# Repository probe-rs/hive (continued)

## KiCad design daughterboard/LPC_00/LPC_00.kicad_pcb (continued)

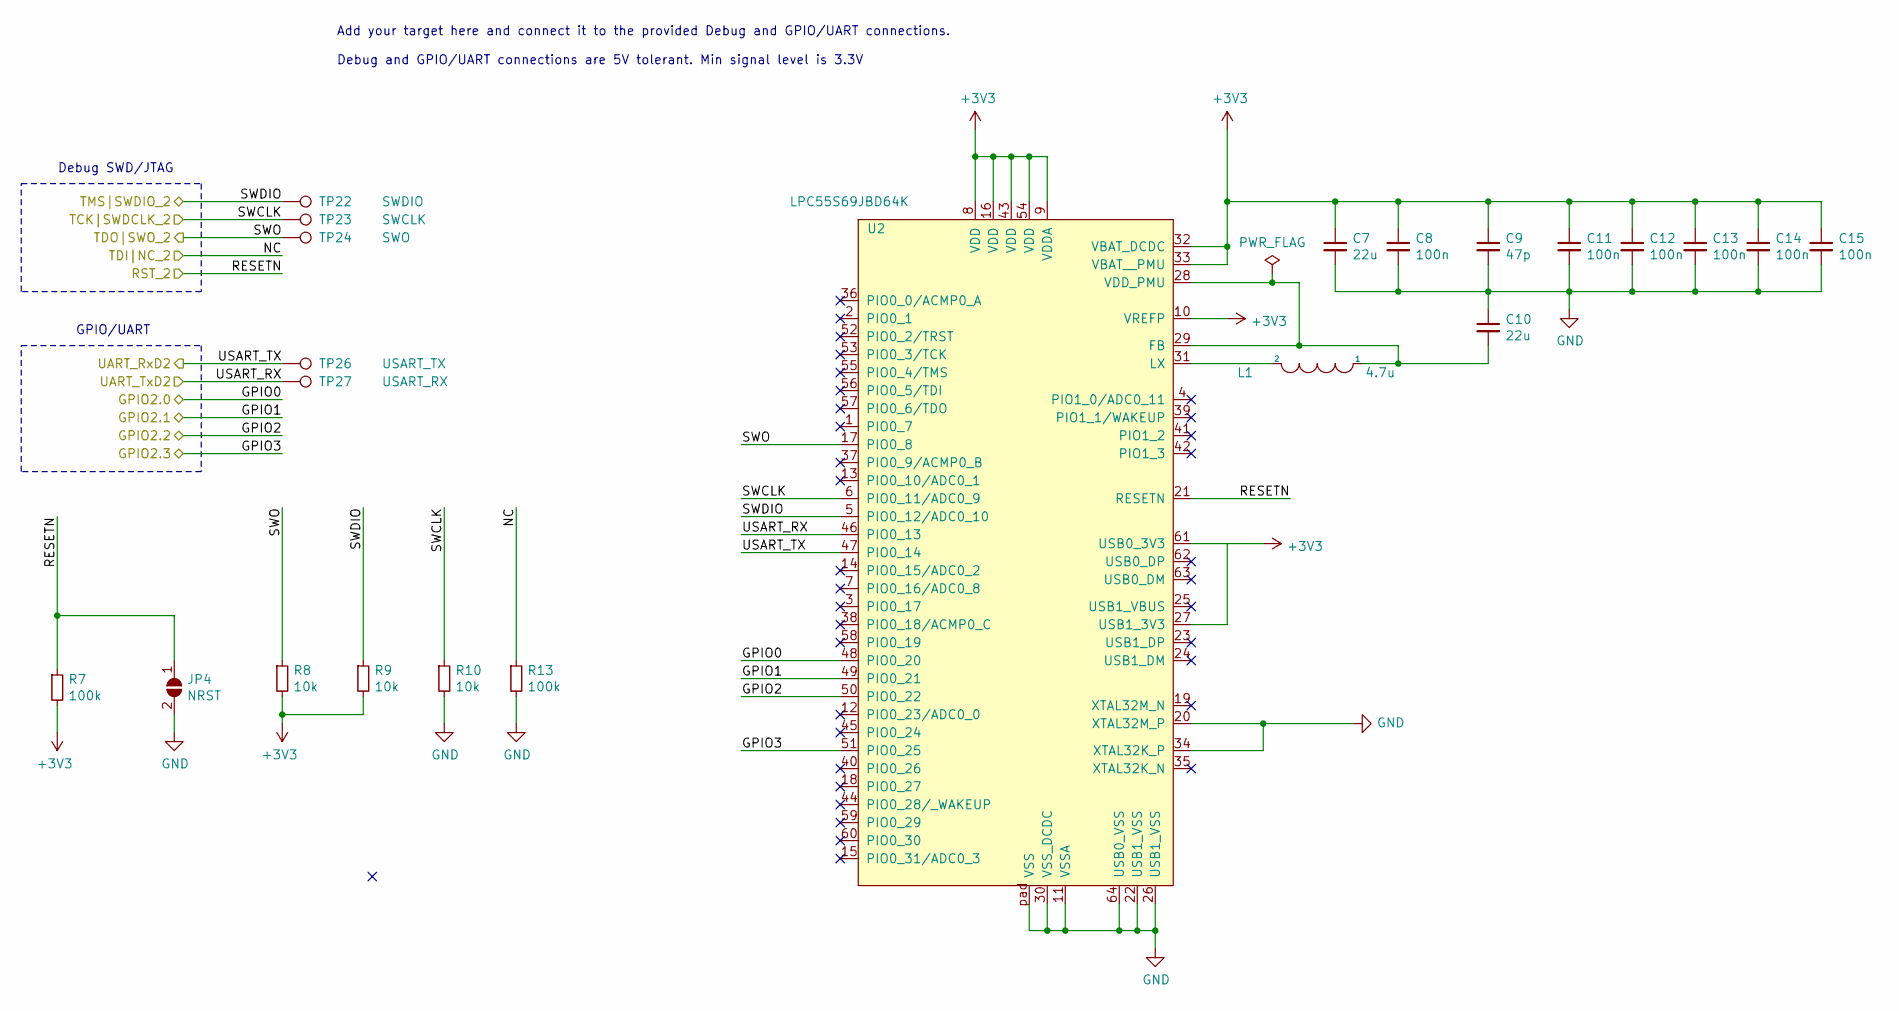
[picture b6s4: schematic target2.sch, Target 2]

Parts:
C7, C10: 22u; C_0603_1608Metric_Pad1.05x0.95mm_HandSolder
C8, C11, C12, C13, C14, C15: 100n; C_0603_1608Metric_Pad1.05x0.95mm_HandSolder
C9: 47p; C_0603_1608Metric_Pad1.05x0.95mm_HandSolder
JP4: NRST; SolderJumper-2_P1.3mm_Open_TrianglePad1.0x1.5mm
L1: 4.7u; TYA40204R7M-10
R7, R13: 100k; R_0603_1608Metric_Pad1.05x0.95mm_HandSolder
R8, R9, R10: 10k; R_0603_1608Metric_Pad1.05x0.95mm_HandSolder
TP22: SWDIO; TestPoint_Pad_1.0x1.0mm
TP23: SWCLK; TestPoint_Pad_1.0x1.0mm
TP24: SWO; TestPoint_Pad_1.0x1.0mm
TP26: USART_TX; TestPoint_Pad_1.0x1.0mm
TP27: USART_RX; TestPoint_Pad_1.0x1.0mm
U2: LPC55S69JBD64K

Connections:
+3V3: C7.1, C8.1, C9.1, C11.1, C12.1, C13.1, C14.1, C15.1, R7.2, R8.2, R9.2, U2.8 (VDD), U2.9 (VDDA), U2.10 (VREFP), U2.16 (VDD), U2.27 (USB1_3V3), U2.32 (VBAT_DCDC), U2.33 (VBAT__PMU), U2.43 (VDD), U2.54 (VDD), U2.61 (USB0_3V3); also elsewhere on the board
/Target 2/GPIO2.0: U2.48 (PIO0_20); also elsewhere on the board
/Target 2/GPIO2.1: U2.49 (PIO0_21); also elsewhere on the board
/Target 2/GPIO2.2: U2.50 (PIO0_22); also elsewhere on the board
/Target 2/GPIO2.3: U2.51 (PIO0_25); also elsewhere on the board
/Target 2/RST_2: JP4.1 (A), R7.1, U2.21 (RESETN); also elsewhere on the board
/Target 2/TCK|SWDCLK_2: R10.1, TP23.1, U2.6 (PIO0_11/ADC0_9); also elsewhere on the board
/Target 2/TDI|NC_2: R13.1; also elsewhere on the board
/Target 2/TDO|SWO_2: R8.1, TP24.1, U2.17 (PIO0_8); also elsewhere on the board
/Target 2/TMS|SWDIO_2: R9.1, TP22.1, U2.5 (PIO0_12/ADC0_10); also elsewhere on the board
/Target 2/UART_RxD2: TP26.1, U2.47 (PIO0_14); also elsewhere on the board
/Target 2/UART_TxD2: TP27.1, U2.46 (PIO0_13); also elsewhere on the board
GND: C7.2, C8.2, C9.2, C10.1, C11.2, C12.2, C13.2, C14.2, C15.2, JP4.2 (B), R10.2, R13.2, U2.11 (VSSA), U2.20 (XTAL32M_P), U2.22 (USB1_VSS), U2.26 (USB1_VSS), U2.30 (VSS_DCDC), U2.34 (XTAL32K_P), U2.64 (USB0_VSS), U2.pad (VSS); also elsewhere on the board
unnamed: C10.2, L1.1, U2.28 (VDD_PMU), U2.29 (FB)
unnamed: L1.2, U2.31 (LX)

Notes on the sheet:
Debug SWD/JTAG
GPIO/UART
Add your target here and connect it to the provided Debug and GPIO/UART connections. Debug and GPIO/UART connections are 5V tolerant. Min signal level is 3.3V

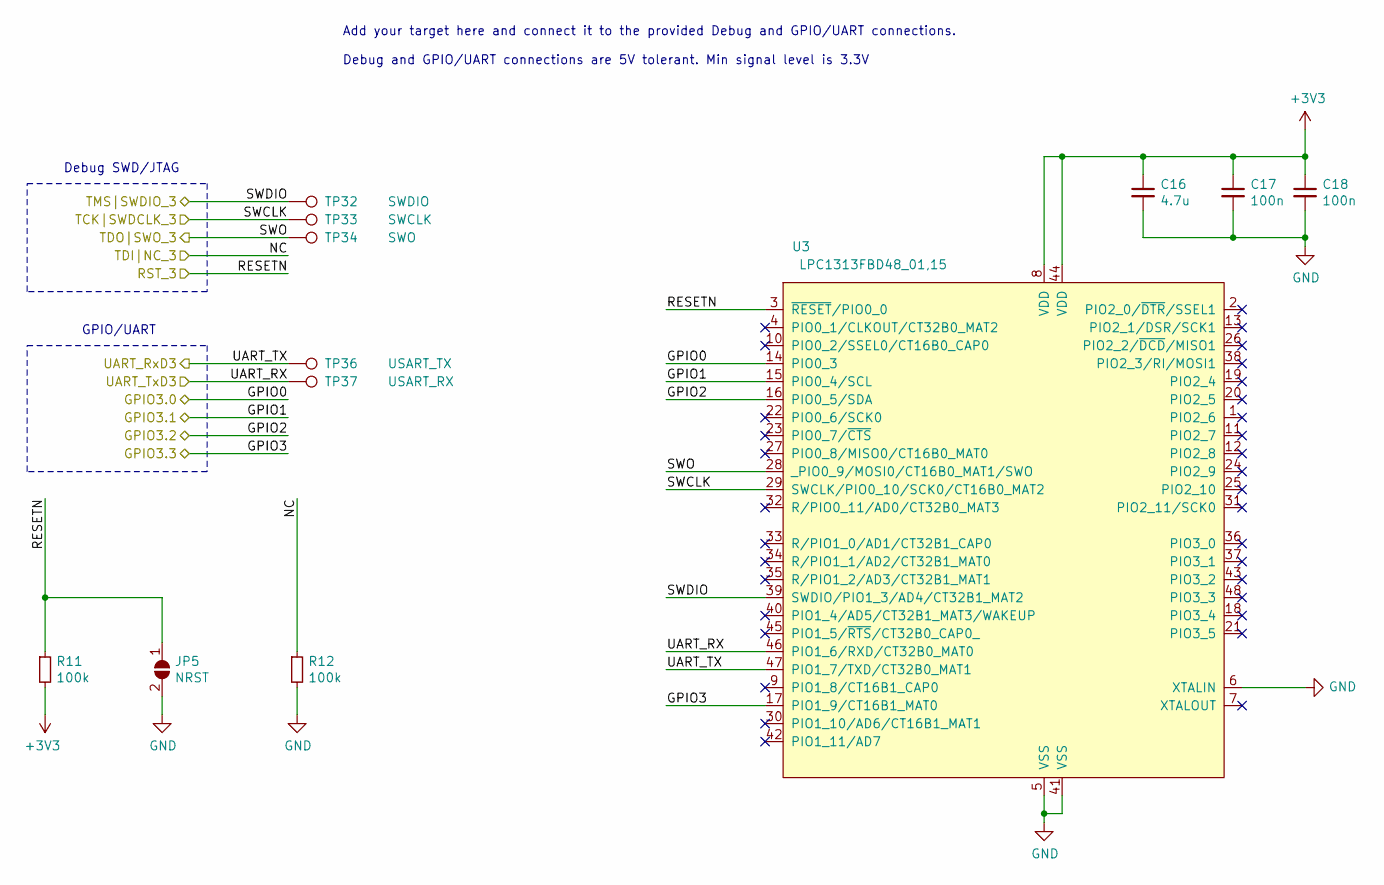
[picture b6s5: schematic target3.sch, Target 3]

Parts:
C16: 4.7u; C_0603_1608Metric_Pad1.05x0.95mm_HandSolder
C17, C18: 100n; C_0603_1608Metric_Pad1.05x0.95mm_HandSolder
JP5: NRST; SolderJumper-2_P1.3mm_Open_TrianglePad1.0x1.5mm
R11, R12: 100k; R_0603_1608Metric_Pad1.05x0.95mm_HandSolder
TP32: SWDIO; TestPoint_Pad_1.0x1.0mm
TP33: SWCLK; TestPoint_Pad_1.0x1.0mm
TP34: SWO; TestPoint_Pad_1.0x1.0mm
TP36: USART_TX; TestPoint_Pad_1.0x1.0mm
TP37: USART_RX; TestPoint_Pad_1.0x1.0mm
U3: LPC1313FBD48_01,15; LPC1313FBD48_0115

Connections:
+3V3: C16.1, C17.1, C18.1, R11.2, U3.8 (VDD), U3.44 (VDD); also elsewhere on the board
/Target 3/GPIO3.0: U3.14 (PIO0_3); also elsewhere on the board
/Target 3/GPIO3.1: U3.15 (PIO0_4/SCL); also elsewhere on the board
/Target 3/GPIO3.2: U3.16 (PIO0_5/SDA); also elsewhere on the board
/Target 3/GPIO3.3: U3.17 (PIO1_9/CT16B1_MAT0); also elsewhere on the board
/Target 3/RST_3: JP5.1 (A), R11.1, U3.3 (~RESET~/PIO0_0); also elsewhere on the board
/Target 3/TCK|SWDCLK_3: TP33.1, U3.29 (SWCLK/PIO0_10/SCK0/CT16B0_MAT2); also elsewhere on the board
/Target 3/TDI|NC_3: R12.1; also elsewhere on the board
/Target 3/TDO|SWO_3: TP34.1, U3.28 (_PIO0_9/MOSI0/CT16B0_MAT1/SWO); also elsewhere on the board
/Target 3/TMS|SWDIO_3: TP32.1, U3.39 (SWDIO/PIO1_3/AD4/CT32B1_MAT2); also elsewhere on the board
/Target 3/UART_RxD3: TP36.1, U3.47 (PIO1_7/TXD/CT32B0_MAT1); also elsewhere on the board
/Target 3/UART_TxD3: TP37.1, U3.46 (PIO1_6/RXD/CT32B0_MAT0); also elsewhere on the board
GND: C16.2, C17.2, C18.2, JP5.2 (B), R12.2, U3.5 (VSS), U3.6 (XTALIN), U3.41 (VSS); also elsewhere on the board

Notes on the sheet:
Debug SWD/JTAG
GPIO/UART
Add your target here and connect it to the provided Debug and GPIO/UART connections. Debug and GPIO/UART connections are 5V tolerant. Min signal level is 3.3V

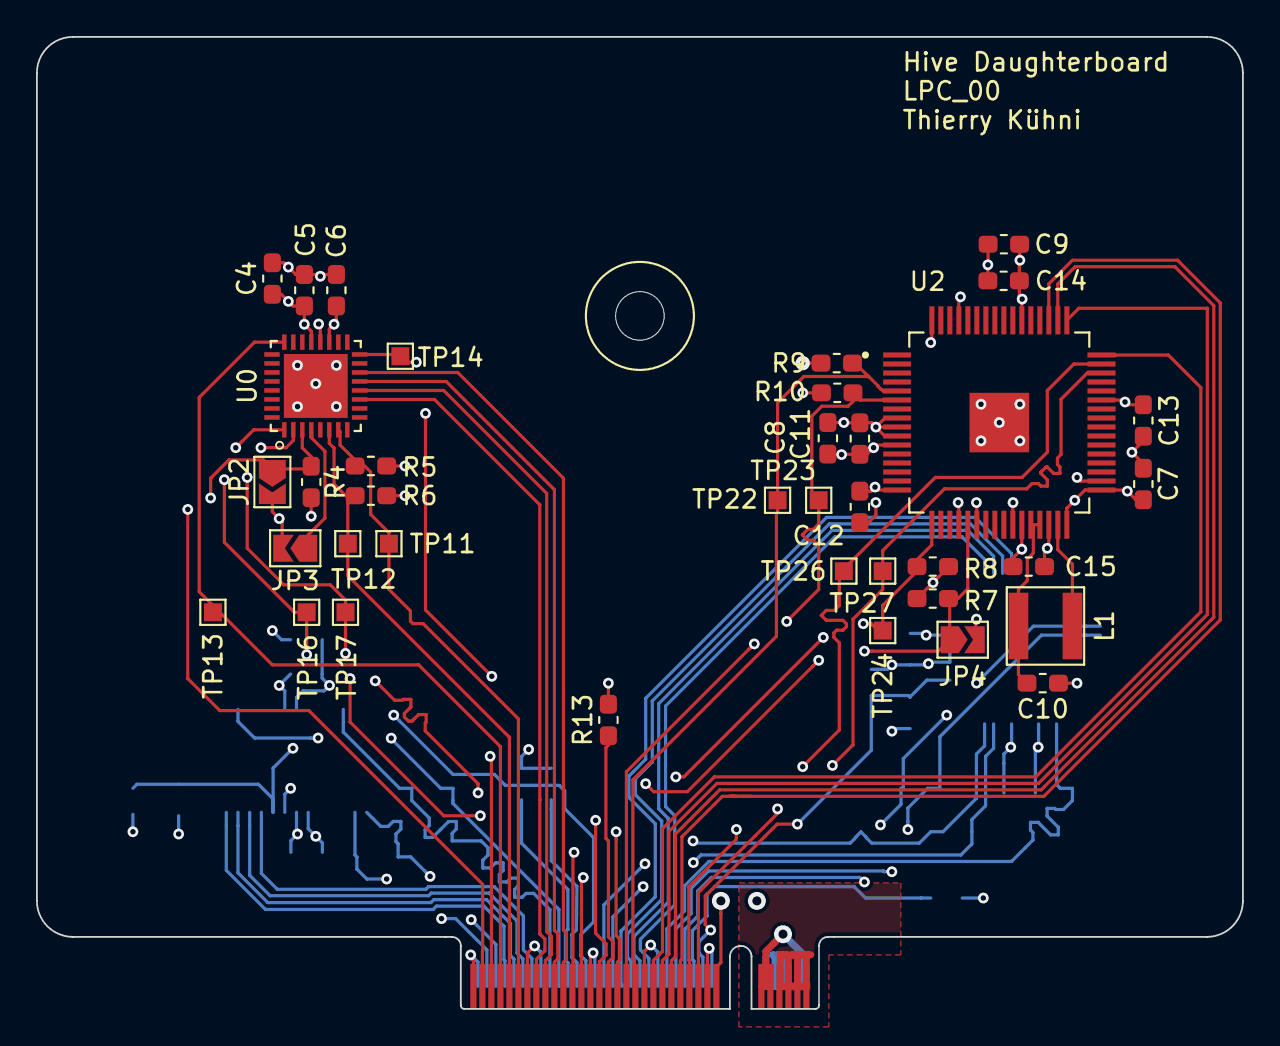
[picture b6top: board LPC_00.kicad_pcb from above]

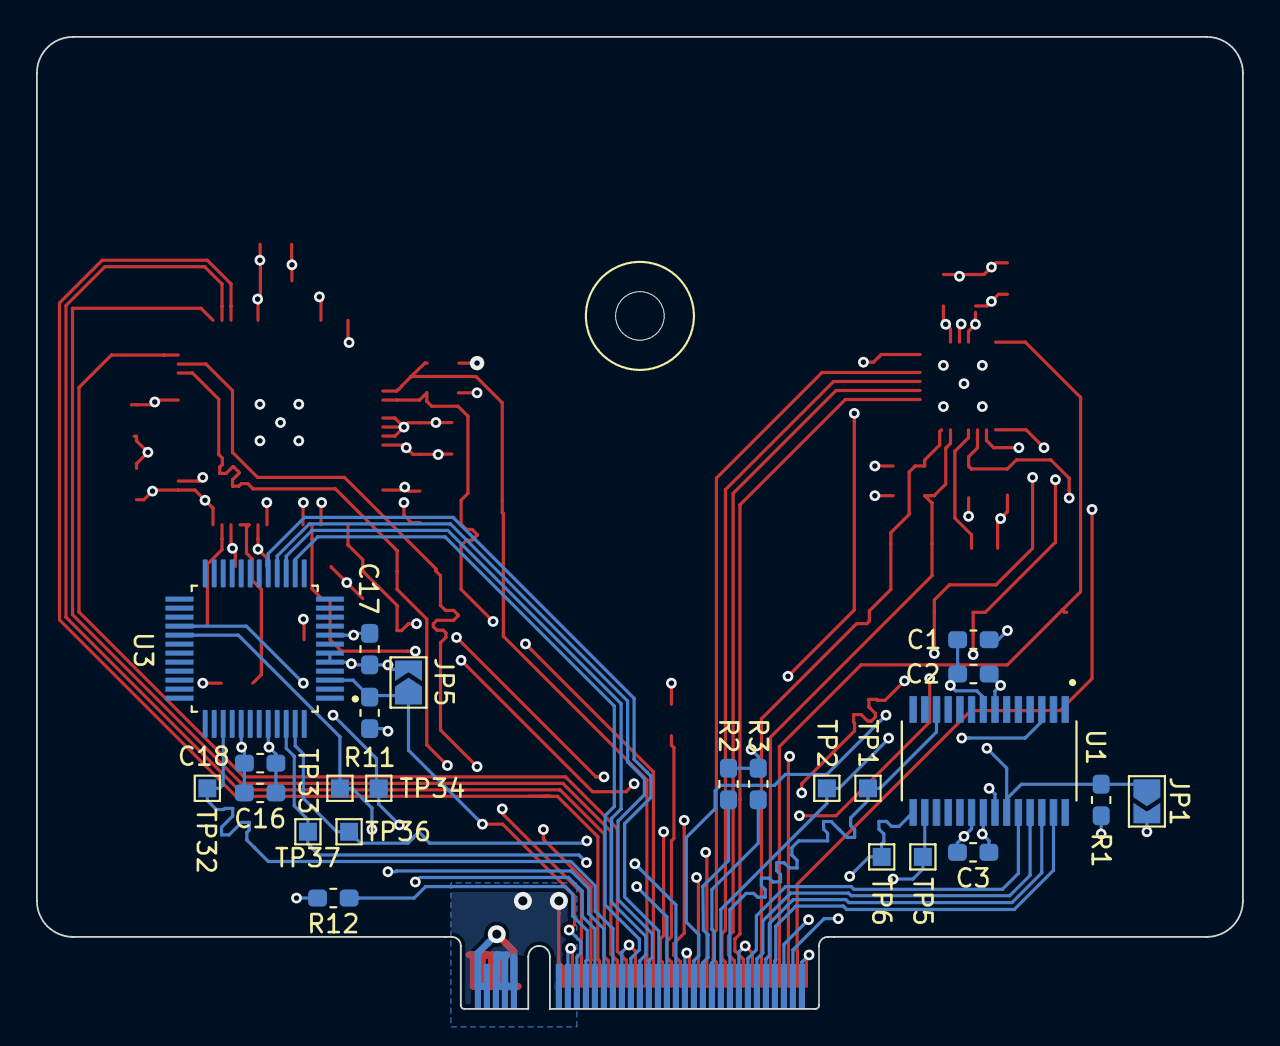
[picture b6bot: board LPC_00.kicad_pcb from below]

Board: 4 copper layers, 67.0 x 54.0 mm, 63 parts (24 on the bottom side), 50 nets.

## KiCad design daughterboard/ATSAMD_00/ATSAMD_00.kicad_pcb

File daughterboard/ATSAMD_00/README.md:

## ATSAMD_00
A daughterboard which contains a selection of ATSAMD MCUs.

### Targets
The following targets are implemented on this Daughterboard:
| Designation | MCU |
| --- | --- |
| target0 | ATSAMD10C13A-SSUT |
| target1 | ATSAMD09D14A-MUT |
| target2 | ATSAMD51J18A-AU |
| target3 | ATSAMD21E16L-AFT |

### Partlist
The partlist for this Daughterboard is available [here](https://octopart.com/bom-tool/9WbPLhTP).

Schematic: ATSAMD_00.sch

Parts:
H1: MountingHoleDaughterboard; MountingHole_2.7mm_M2.5
J1: m2_keyA_67pin_daughterboard; m2_keyB

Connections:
+3V3: J1.6 (+3V3), J1.8 (+3V3), J1.10 (+3V3), J1.20 (+3V3), J1.21 (BOARD_DETECT); also elsewhere on the board
+5V: J1.1 (+5V), J1.3 (+5V), J1.5 (+5V), J1.7 (+5V)
/Target 0/GPIO0.0: J1.61 (TGT_GPIO0.0); also elsewhere on the board
/Target 0/GPIO0.1: J1.59 (TGT_GPIO0.1); also elsewhere on the board
/Target 0/GPIO0.2: J1.57 (TGT_GPIO0.2); also elsewhere on the board
/Target 0/GPIO0.3: J1.55 (TGT_GPIO0.3); also elsewhere on the board
/Target 0/RST_0: J1.73 (TGT_RST_0); also elsewhere on the board
/Target 0/TCK|SWDCLK_0: J1.67 (TGT_TCK|SWDCLK_0); also elsewhere on the board
/Target 0/TDI|NC_0: J1.71 (TGT_TDI|NC_0); also elsewhere on the board
/Target 0/TDO|SWO_0: J1.69 (TGT_TDO|SWO_0); also elsewhere on the board
/Target 0/TMS|SWDIO_0: J1.65 (TGT_TMS|SWDIO_0); also elsewhere on the board
/Target 0/UART_RxD0: J1.51 (TGT_UART_RxD0); also elsewhere on the board
/Target 0/UART_TxD0: J1.53 (TGT_UART_TxD0); also elsewhere on the board
/Target 1/GPIO1.0: J1.62 (TGT_GPIO1.0); also elsewhere on the board
/Target 1/GPIO1.1: J1.64 (TGT_GPIO1.1); also elsewhere on the board
/Target 1/GPIO1.2: J1.66 (TGT_GPIO1.2); also elsewhere on the board
/Target 1/GPIO1.3: J1.68 (TGT_GPIO1.3); also elsewhere on the board
/Target 1/RST_1: J1.50 (TGT_RST_1); also elsewhere on the board
/Target 1/TCK|SWDCLK_1: J1.56 (TGT_TCK|SWDCLK_1); also elsewhere on the board
/Target 1/TDI|NC_1: J1.52 (TGT_TDI|NC_1); also elsewhere on the board
/Target 1/TDO|SWO_1: J1.54 (TGT_TDO|SWO_1); also elsewhere on the board
/Target 1/TMS|SWDIO_1: J1.58 (TGT_TMS|SWDIO_1); also elsewhere on the board
/Target 1/UART_RxD1: J1.72 (TGT_UART_RxD1); also elsewhere on the board
/Target 1/UART_TxD1: J1.70 (TGT_UART_TxD1); also elsewhere on the board
/Target 2/GPIO2.0: J1.35 (TGT_GPIO2.0); also elsewhere on the board
/Target 2/GPIO2.1: J1.33 (TGT_GPIO2.1); also elsewhere on the board
/Target 2/GPIO2.2: J1.31 (TGT_GPIO2.2); also elsewhere on the board
/Target 2/GPIO2.3: J1.29 (TGT_GPIO2.3); also elsewhere on the board
/Target 2/RST_2: J1.47 (TGT_RST_2); also elsewhere on the board
/Target 2/TCK|SWDCLK_2: J1.41 (TGT_TCK|SWDCLK_2); also elsewhere on the board
/Target 2/TDI|NC_2: J1.45 (TGT_TDI|NC_2); also elsewhere on the board
/Target 2/TDO|SWO_2: J1.43 (TGT_TDO|SWO_2); also elsewhere on the board
/Target 2/TMS|SWDIO_2: J1.39 (TGT_TMS|SWDIO_2); also elsewhere on the board
/Target 2/UART_RxD2: J1.25 (TGT_UART_RxD2); also elsewhere on the board
/Target 2/UART_TxD2: J1.27 (TGT_UART_TxD2); also elsewhere on the board
/Target 3/GPIO3.0: J1.36 (TGT_GPIO3.0); also elsewhere on the board
/Target 3/GPIO3.1: J1.38 (TGT_GPIO3.1); also elsewhere on the board
/Target 3/GPIO3.2: J1.40 (TGT_GPIO3.2); also elsewhere on the board
/Target 3/GPIO3.3: J1.42 (TGT_GPIO3.3); also elsewhere on the board
/Target 3/RST_3: J1.24 (TGT_RST_3); also elsewhere on the board
/Target 3/TCK|SWDCLK_3: J1.30 (TGT_TCK|SWDCLK_3); also elsewhere on the board
/Target 3/TDI|NC_3: J1.26 (TGT_TDI|NC_3); also elsewhere on the board
/Target 3/TDO|SWO_3: J1.28 (TGT_TDO|SWO_3); also elsewhere on the board
/Target 3/TMS|SWDIO_3: J1.32 (TGT_TMS|SWDIO_3); also elsewhere on the board
/Target 3/UART_RxD3: J1.46 (TGT_UART_RxD3); also elsewhere on the board
/Target 3/UART_TxD3: J1.44 (TGT_UART_TxD3); also elsewhere on the board
GND: J1.2 (GND), J1.4 (GND), J1.9 (GND), J1.11 (GND), J1.22 (GND), J1.23 (GND), J1.34 (GND), J1.37 (GND), J1.48 (GND), J1.49 (GND), J1.60 (GND), J1.63 (GND), J1.74 (GND), J1.75 (GND); also elsewhere on the board

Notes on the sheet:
You can implement 4 targets per daugtherboard. Please use the corresponding hierarchical schematics for that.

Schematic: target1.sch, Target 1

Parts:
C1, C3: 100n; C_0603_1608Metric_Pad1.05x0.95mm_HandSolder
C2: 4.7u; C_0603_1608Metric_Pad1.05x0.95mm_HandSolder
JP1: NRST; SolderJumper-2_P1.3mm_Open_TrianglePad1.0x1.5mm
R1: 10k; R_0603_1608Metric_Pad1.05x0.95mm_HandSolder
R2: 330; R_0603_1608Metric_Pad1.05x0.95mm_HandSolder
R3: 1k; R_0603_1608Metric_Pad1.05x0.95mm_HandSolder
R4, R5: 100k; R_0603_1608Metric_Pad1.05x0.95mm_HandSolder
TP1: SWDIO; TestPoint_Pad_1.0x1.0mm
TP2: SWCLK; TestPoint_Pad_1.0x1.0mm
TP5: USART_TX; TestPoint_Pad_1.0x1.0mm
TP6: USART_RX; TestPoint_Pad_1.0x1.0mm
U1: ATSAMD09D14A-M; QFN-24-1EP_4x4mm_P0.5mm_EP2.6x2.6mm

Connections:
+3V3: C2.1, C3.1, R1.2, R3.2, U1.24 (VDD); also elsewhere on the board
/Target 1/GPIO1.0: U1.9 (PA10); also elsewhere on the board
/Target 1/GPIO1.1: U1.10 (PA11); also elsewhere on the board
/Target 1/GPIO1.2: U1.11 (PA14); also elsewhere on the board
/Target 1/GPIO1.3: U1.12 (PA15); also elsewhere on the board
/Target 1/RST_1: C1.1, R1.1, R2.2, U1.18 (PA28/~RST); also elsewhere on the board
/Target 1/TCK|SWDCLK_1: R3.1, TP2.1, U1.19 (PA30/SWCLK); also elsewhere on the board
/Target 1/TDI|NC_1: R4.1; also elsewhere on the board
/Target 1/TDO|SWO_1: R5.1; also elsewhere on the board
/Target 1/TMS|SWDIO_1: TP1.1, U1.20 (PA31/SWDIO); also elsewhere on the board
/Target 1/UART_RxD1: TP5.1, U1.3 (PA04); also elsewhere on the board
/Target 1/UART_TxD1: TP6.1, U1.5 (PA06); also elsewhere on the board
GND: C1.2, C2.2, C3.2, JP1.1 (A), R4.2, R5.2, U1.23 (GND); also elsewhere on the board
unnamed: JP1.2 (B), R2.1

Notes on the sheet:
Debug SWD/JTAG
GPIO/UART
Add your target here and connect it to the provided Debug and GPIO/UART connections. Debug and GPIO/UART connections are 5V tolerant. Min signal level is 3.3V

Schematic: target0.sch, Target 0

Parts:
C4, C6: 100n; C_0603_1608Metric_Pad1.05x0.95mm_HandSolder
C5: 4.7u; C_0603_1608Metric_Pad1.05x0.95mm_HandSolder
JP2: NRST; SolderJumper-2_P1.3mm_Open_TrianglePad1.0x1.5mm
R6: 10k; R_0603_1608Metric_Pad1.05x0.95mm_HandSolder
R7: 330; R_0603_1608Metric_Pad1.05x0.95mm_HandSolder
R8: 1k; R_0603_1608Metric_Pad1.05x0.95mm_HandSolder
R9, R10: 100k; R_0603_1608Metric_Pad1.05x0.95mm_HandSolder
TP11: SWDIO; TestPoint_Pad_1.0x1.0mm
TP12: SWCLK; TestPoint_Pad_1.0x1.0mm
TP15: USART_TX; TestPoint_Pad_1.0x1.0mm
TP16: USART_RX; TestPoint_Pad_1.0x1.0mm
U0: ATSAMD10C13A-SS; SOIC-14_3.9x8.7mm_P1.27mm

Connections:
+3V3: C5.1, C6.1, R6.2, R8.2, U0.12 (VDD); also elsewhere on the board
/Target 0/GPIO0.0: U0.9 (PA24); also elsewhere on the board
/Target 0/GPIO0.1: U0.10 (PA25); also elsewhere on the board
/Target 0/GPIO0.2: U0.13 (PA02); also elsewhere on the board
/Target 0/GPIO0.3: U0.14 (PA04); also elsewhere on the board
/Target 0/RST_0: C4.1, R6.1, R7.2, U0.6 (PA28/~RST); also elsewhere on the board
/Target 0/TCK|SWDCLK_0: R8.1, TP12.1, U0.7 (PA30/SWCLK); also elsewhere on the board
/Target 0/TDI|NC_0: R9.1; also elsewhere on the board
/Target 0/TDO|SWO_0: R10.1; also elsewhere on the board
/Target 0/TMS|SWDIO_0: TP11.1, U0.8 (PA31/SWDIO); also elsewhere on the board
/Target 0/UART_RxD0: TP15.1, U0.4 (PA14); also elsewhere on the board
/Target 0/UART_TxD0: TP16.1, U0.1 (PA05); also elsewhere on the board
GND: C4.2, C5.2, C6.2, JP2.1 (A), R9.2, R10.2, U0.11 (GND); also elsewhere on the board
unnamed: JP2.2 (B), R7.1

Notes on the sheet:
Debug SWD/JTAG
GPIO/UART
Add your target here and connect it to the provided Debug and GPIO/UART connections. Debug and GPIO/UART connections are 5V tolerant. Min signal level is 3.3V

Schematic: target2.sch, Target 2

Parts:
C7, C8, C12, C13, C14, C20: 100n; C_0603_1608Metric_Pad1.05x0.95mm_HandSolder
C9: 4.7u; C_0603_1608Metric_Pad1.05x0.95mm_HandSolder
C10: 10u; C_0603_1608Metric_Pad1.05x0.95mm_HandSolder
C11: 1u; C_0603_1608Metric_Pad1.05x0.95mm_HandSolder
JP3: NRST; SolderJumper-2_P1.3mm_Open_TrianglePad1.0x1.5mm
R11: 10k; R_0603_1608Metric_Pad1.05x0.95mm_HandSolder
R12: 330; R_0603_1608Metric_Pad1.05x0.95mm_HandSolder
R13: 1k; R_0603_1608Metric_Pad1.05x0.95mm_HandSolder
R14: 100k; R_0603_1608Metric_Pad1.05x0.95mm_HandSolder
TP21: SWDIO; TestPoint_Pad_1.0x1.0mm
TP22: SWCLK; TestPoint_Pad_1.0x1.0mm
TP23: SWO; TestPoint_Pad_1.0x1.0mm
TP25: USART_TX; TestPoint_Pad_1.0x1.0mm
TP26: USART_RX; TestPoint_Pad_1.0x1.0mm
U2: ATSAMD51J18A-A; TQFP-64_10x10mm_P0.5mm

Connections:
+3V3: C10.1, C11.1, C12.1, C13.1, C14.1, C20.1, R11.2, R13.2, U2.8 (VDDANA), U2.21 (VDDIOB), U2.34 (VDDIO), U2.48 (VDDIO), U2.56 (VDDIO); also elsewhere on the board
/Target 2/GPIO2.0: U2.1 (PA00); also elsewhere on the board
/Target 2/GPIO2.1: U2.2 (PA01); also elsewhere on the board
/Target 2/GPIO2.2: U2.3 (PA02); also elsewhere on the board
/Target 2/GPIO2.3: U2.4 (PA03); also elsewhere on the board
/Target 2/RST_2: C7.1, R11.1, R12.2, U2.52 (~RESET); also elsewhere on the board
/Target 2/TCK|SWDCLK_2: R13.1, TP22.1, U2.57 (PA30); also elsewhere on the board
/Target 2/TDI|NC_2: R14.1; also elsewhere on the board
/Target 2/TDO|SWO_2: TP23.1, U2.59 (PB30); also elsewhere on the board
/Target 2/TMS|SWDIO_2: TP21.1, U2.58 (PA31); also elsewhere on the board
/Target 2/UART_RxD2: TP25.1, U2.35 (PA16); also elsewhere on the board
/Target 2/UART_TxD2: TP26.1, U2.37 (PA18); also elsewhere on the board
GND: C7.2, C8.2, C9.2, C10.2, C11.2, C12.2, C13.2, C14.2, C20.2, JP3.1 (A), R14.2, U2.7 (GNDANA), U2.22 (GND), U2.33 (GND), U2.47 (GND), U2.54 (GND); also elsewhere on the board
unnamed: C8.1, C9.1, U2.53 (VDDCORE)
unnamed: JP3.2 (B), R12.1

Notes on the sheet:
Debug SWD/JTAG
GPIO/UART
Add your target here and connect it to the provided Debug and GPIO/UART connections. Debug and GPIO/UART connections are 5V tolerant. Min signal level is 3.3V

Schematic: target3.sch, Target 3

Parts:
C15, C18, C19: 100n; C_0603_1608Metric_Pad1.05x0.95mm_HandSolder
C16: 1u; C_0603_1608Metric_Pad1.05x0.95mm_HandSolder
C17: 10u; C_0603_1608Metric_Pad1.05x0.95mm_HandSolder
JP4: NRST; SolderJumper-2_P1.3mm_Open_TrianglePad1.0x1.5mm
R15: 10k; R_0603_1608Metric_Pad1.05x0.95mm_HandSolder
R16: 330; R_0603_1608Metric_Pad1.05x0.95mm_HandSolder
R17: 1k; R_0603_1608Metric_Pad1.05x0.95mm_HandSolder
R18, R19: 100k; R_0603_1608Metric_Pad1.05x0.95mm_HandSolder
TP31: SWDIO; TestPoint_Pad_1.0x1.0mm
TP32: SWCLK; TestPoint_Pad_1.0x1.0mm
TP35: USART_TX; TestPoint_Pad_1.0x1.0mm
TP36: USART_RX; TestPoint_Pad_1.0x1.0mm
U3: ATSAMD21E16L-AFT

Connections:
+3V3: C17.1, C18.1, C19.1, R15.2, R17.2, U3.9 (VDDIO/ANA), U3.28 (VDDIO); also elsewhere on the board
/Target 3/GPIO3.0: U3.17 (PA16); also elsewhere on the board
/Target 3/GPIO3.1: U3.18 (PA17); also elsewhere on the board
/Target 3/GPIO3.2: U3.19 (PA18); also elsewhere on the board
/Target 3/GPIO3.3: U3.20 (PA19); also elsewhere on the board
/Target 3/RST_3: C15.1, R15.1, R16.2, U3.25 (~RESET~); also elsewhere on the board
/Target 3/TCK|SWDCLK_3: R17.1, TP32.1, U3.29 (PA30); also elsewhere on the board
/Target 3/TDI|NC_3: R18.1; also elsewhere on the board
/Target 3/TDO|SWO_3: R19.1; also elsewhere on the board
/Target 3/TMS|SWDIO_3: TP31.1, U3.30 (PA31); also elsewhere on the board
/Target 3/UART_RxD3: TP35.1, U3.11 (PA08); also elsewhere on the board
/Target 3/UART_TxD3: TP36.1, U3.13 (PA10); also elsewhere on the board
GND: C15.2, C16.2, C17.2, C18.2, C19.2, JP4.1 (A), R18.2, R19.2, U3.10 (GND), U3.26 (GND); also elsewhere on the board
unnamed: C16.1, U3.27 (VDDCORE)
unnamed: JP4.2 (B), R16.1

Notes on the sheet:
Debug SWD/JTAG
GPIO/UART
Add your target here and connect it to the provided Debug and GPIO/UART connections. Debug and GPIO/UART connections are 5V tolerant. Min signal level is 3.3V

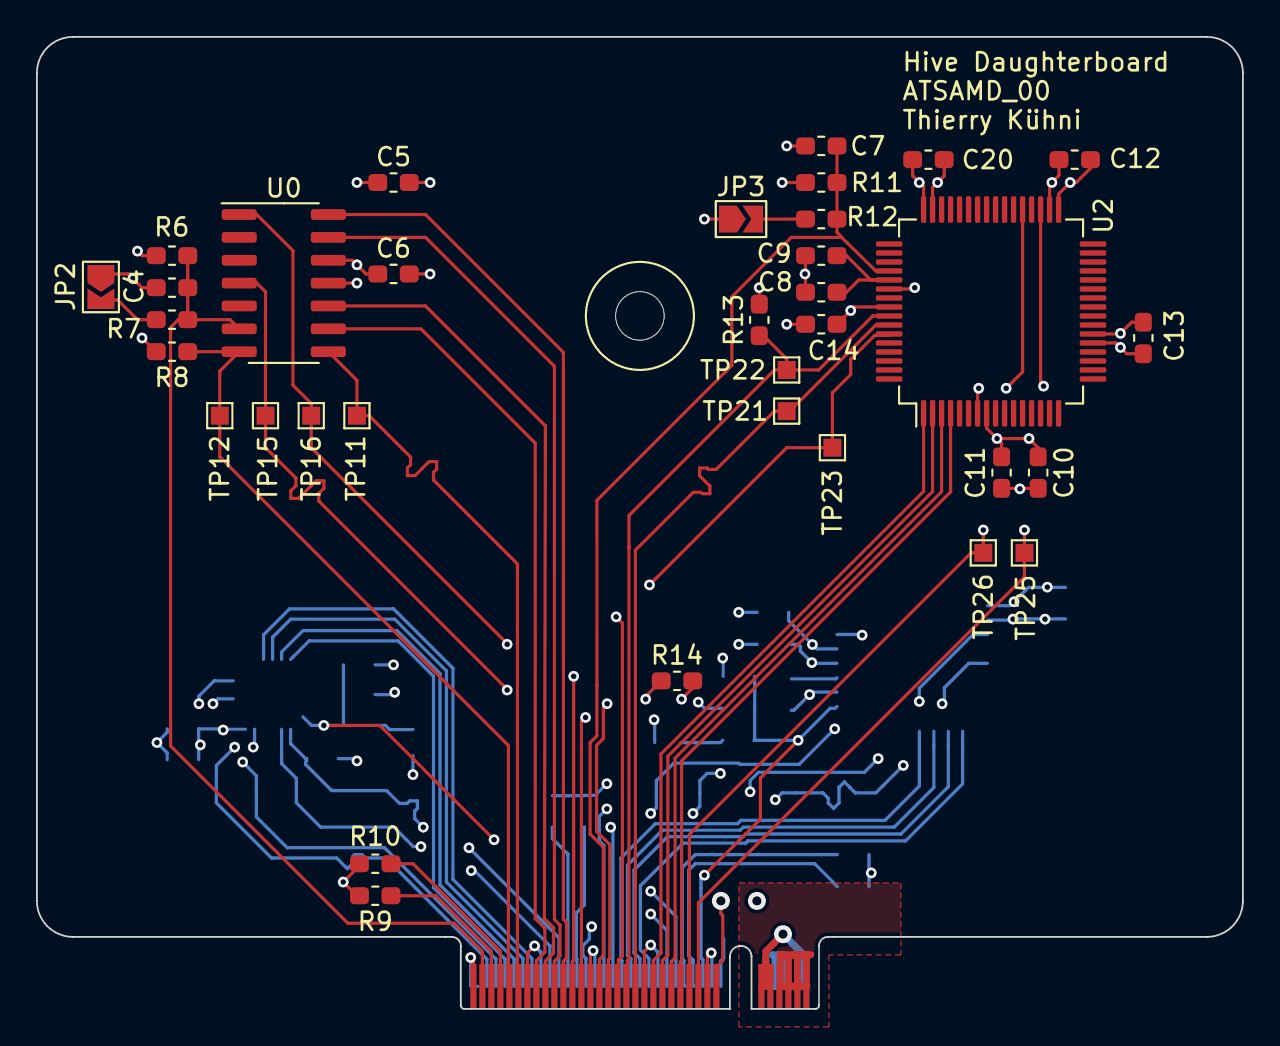
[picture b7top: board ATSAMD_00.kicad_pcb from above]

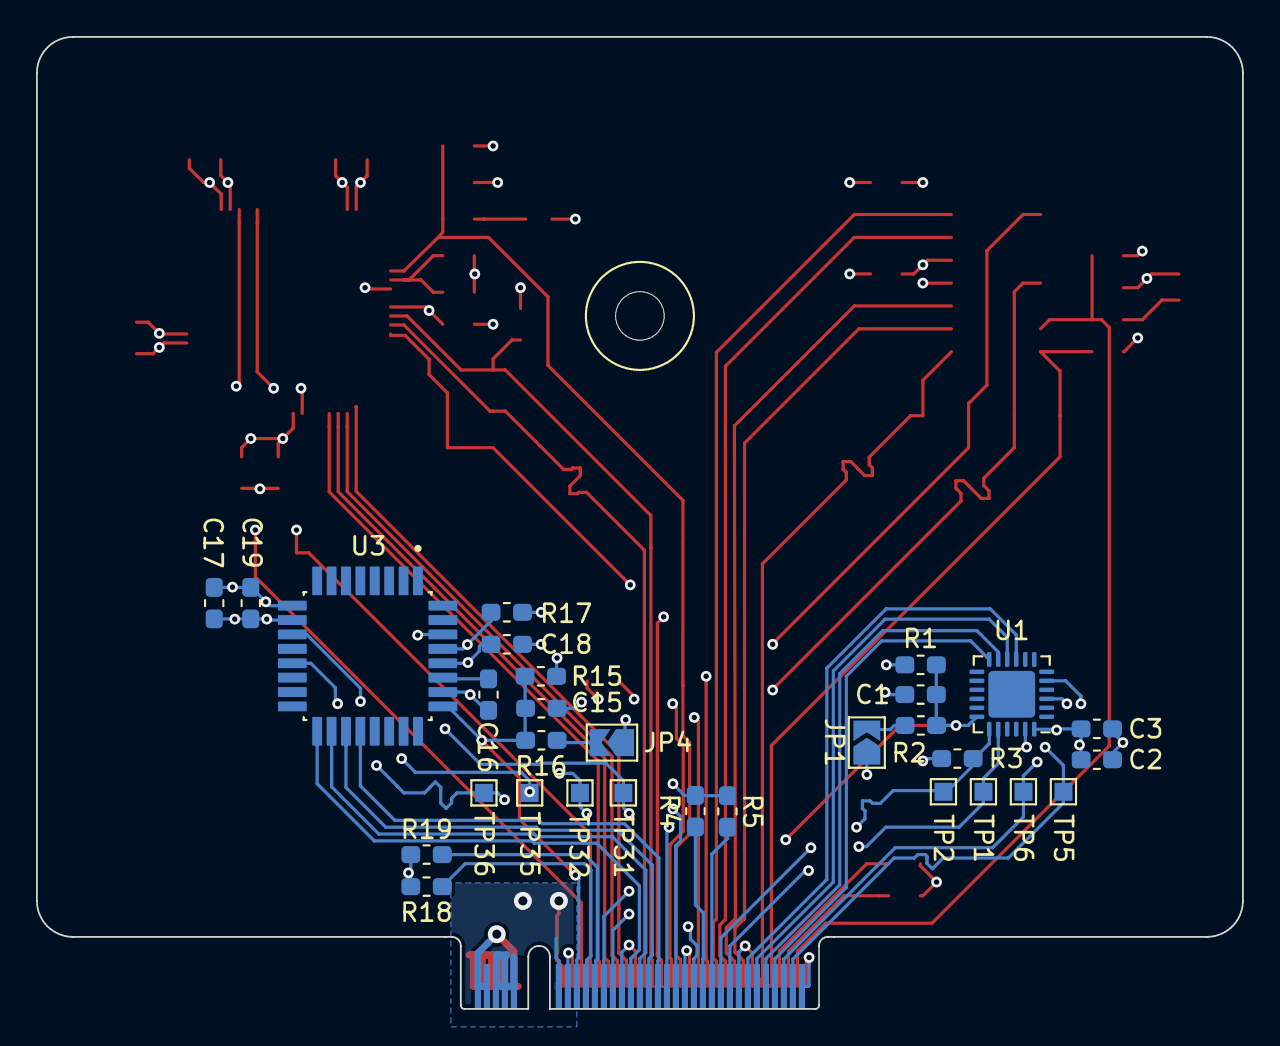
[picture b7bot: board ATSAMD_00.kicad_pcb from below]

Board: 4 copper layers, 67.0 x 54.0 mm, 66 parts (30 on the bottom side), 53 nets.

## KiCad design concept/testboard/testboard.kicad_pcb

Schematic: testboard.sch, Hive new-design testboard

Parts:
C1, C2: 100n; C_0805_2012Metric_Pad1.15x1.40mm_HandSolder
C3, C4: 10u; C_1206_3216Metric_Pad1.42x1.75mm_HandSolder
IC1: NCP1117DT33T5G; TO229P990X238-4N; Mouser Part Number 863-NCP1117DT33T5G
J1: Probe out 1; PinHeader_1x05_P2.54mm_Vertical
J2: I2C; PinHeader_1x02_P2.54mm_Vertical
J3: Probe out 0; PinHeader_1x05_P2.54mm_Vertical
J4: probe connector; SAMTEC_FTSH-105-01-F-DV-007; PARTREV R
J5: IO bank 0; PinHeader_1x08_P2.54mm_Vertical
J6: IO bank 1; PinHeader_1x08_P2.54mm_Vertical
J7: 5V; PinHeader_1x02_P2.54mm_Vertical
JP1: 5V 1B1; PinHeader_1x02_P2.54mm_Vertical
JP2: 1OE; PinHeader_1x02_P2.54mm_Vertical
JP3: 2OE; PinHeader_1x02_P2.54mm_Vertical
JP4: 5V 1A1; PinHeader_1x02_P2.54mm_Vertical
JP5: 1OE IO; SolderJumper-2_P1.3mm_Open_Pad1.0x1.5mm
JP6: 2OE IO; SolderJumper-2_P1.3mm_Open_Pad1.0x1.5mm
JP7: I2C SW SDA; SolderJumper-2_P1.3mm_Open_Pad1.0x1.5mm
JP8: I2C SW SCL; SolderJumper-2_P1.3mm_Open_Pad1.0x1.5mm
R1, R2, R3, R4, R5, R6: 100k; R_0805_2012Metric_Pad1.15x1.40mm_HandSolder
R7, R8: 4k7; R_0805_2012Metric_Pad1.15x1.40mm_HandSolder
S1: Address Switch 0-7; SW_RDS-10S-74385-SMT; PARTREV 1.0
U1: SN74CB3T16211DGGR; SOP50P810X120-56N; MPN SN74CB3T16211DGGR
U2: PCA9535CPW,118; SOP65P640X110-24N; MPN PCA9535CPW,118

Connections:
+3V3: C1.2, C2.2, C3.1, IC1.4 (OUT_TAB), J4.01 (VREF), R2.1, R3.1, R7.2, R8.2, S1.C_1 (C), S1.C_2 (C), U1.17 (VCC), U2.24 (VDD)
+5V: C4.1, IC1.3 (IN), J7.2, JP1.2, JP4.1
/I2C_SCL_in: J2.2, JP8.1, U1.9 (1A7)
/I2C_SCL_out: JP8.2, R8.1, U1.47 (1B7), U2.22 (SCL)
/I2C_SDA_in: J2.1, JP7.1, U1.7 (1A6)
/I2C_SDA_out: JP7.2, R7.1, U1.48 (1B6), U2.23 (SDA)
/IO1_0: J6.1, JP5.1 (A), U2.13 (IO1_0)
/IO1_1: J6.2, JP6.1 (A), U2.14 (IO1_1)
/IO1_2: J6.3, U2.15 (IO1_2)
/IO1_3: J6.4, U2.16 (IO1_3)
/IO1_4: J6.5, U2.17 (IO1_4)
/IO1_5: J6.6, U2.18 (IO1_5)
/IO1_6: J6.7, U2.19 (IO1_6)
/IO1_7: J6.8, U2.20 (IO1_7)
GND: C1.1, C2.1, C3.2, C4.2, IC1.1 (GND), J4.03 (GND), J4.05 (GND), J4.09 (GND_detect), J7.1, JP2.1, JP3.1, R1.1, R4.1, R5.1, R6.1, U1.8 (GND_4), U1.19 (GND_2), U1.38 (GND_3), U1.49 (GND), U2.1 (~INT), U2.12 (VSS)
unnamed: J1.1, U1.10 (1A8)
unnamed: J1.2, U1.11 (1A9)
unnamed: J1.3, U1.12 (1A10)
unnamed: J1.4, U1.13 (1A11)
unnamed: J1.5, U1.14 (1A12)
unnamed: J3.1, U1.33 (2B8), U1.46 (1B8)
unnamed: J3.2, U1.32 (2B9), U1.45 (1B9)
unnamed: J3.3, U1.31 (2B10), U1.44 (1B10)
unnamed: J3.4, U1.30 (2B11), U1.43 (1B11)
unnamed: J3.5, U1.29 (2B12), U1.42 (1B12)
unnamed: J4.02 (SWDIO/TMS), U1.24 (2A8)
unnamed: J4.04 (SWDCLK/TCK), U1.25 (2A9)
unnamed: J4.06 (SWO/TDO), U1.26 (2A10)
unnamed: J4.08 (NC/TDI), U1.27 (2A11)
unnamed: J4.10 (~RESET~), U1.28 (2A12)
unnamed: J5.1, U2.4 (IO0_0)
unnamed: J5.2, U2.5 (IO0_1)
unnamed: J5.3, U2.6 (IO0_2)
unnamed: J5.4, U2.7 (IO0_3)
unnamed: J5.5, U2.8 (IO0_4)
unnamed: J5.6, U2.9 (IO0_5)
unnamed: J5.7, U2.10 (IO0_6)
unnamed: J5.8, U2.11 (IO0_7)
unnamed: JP1.1, R1.2, U1.54 (1B1)
unnamed: JP2.2, JP5.2 (B), R3.2, U1.56 (1~OE)
unnamed: JP3.2, JP6.2 (B), R2.2, U1.55 (2~OE)
unnamed: JP4.2, U1.2 (1A1)
unnamed: R4.2, S1.4, U2.3 (A2)
unnamed: R5.2, S1.2, U2.2 (A1)
unnamed: R6.2, S1.1, U2.21 (A0)

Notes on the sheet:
5V to 3.3V LDO

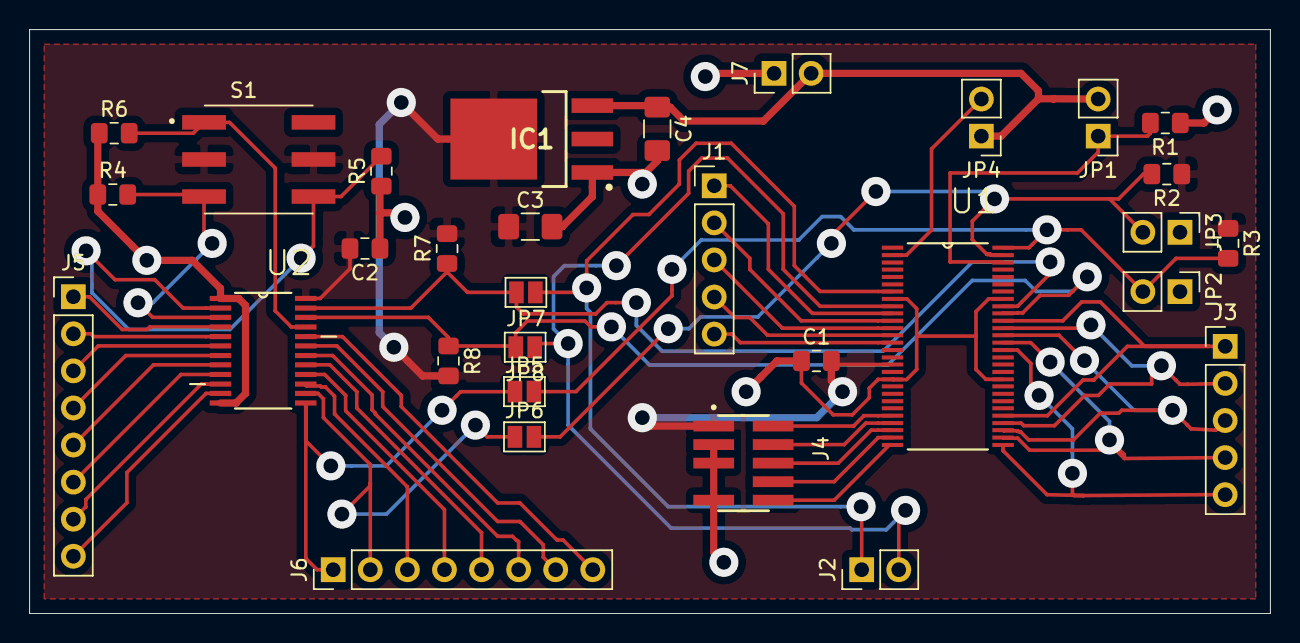
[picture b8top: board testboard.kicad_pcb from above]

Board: 2 copper layers, 85.0 x 40.0 mm, 31 parts (0 on the bottom side), 45 nets.

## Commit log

2020-04-24 Initial design
2020-11-14 pretty much done with routing
2020-11-14 Fix DRC
2020-11-14 Add 3d model and structure diagram
2020-11-14 Make PCB connections sturdier by making the PCB extend under the connectors
2020-11-14 Add a line buffer/multiplexer to RST
2020-11-14 Restructure files
2020-11-15 Add caps & get rid of the jumpers & add two more GND lanes to the connector & remove two OE select signals
2020-11-17 Remade 8channel board
2020-11-21 Fixes
2020-11-21 Now with LDO per 8 channel board
2020-11-21 Add OE pulldown
2020-11-21 8 lanes routed
2020-11-21 Silk fix
2020-11-21 Removed 3 lanes
2020-11-21 Add a daughterboard template
2020-11-21 Use an angled connector
2020-11-22 Update the 3d assembly
2020-11-22 More distance between lanes
2021-07-07 Add cache files
2021-09-17 added concept drawings
2021-09-17 correction of drawing
2021-09-18 Modified concept, added all connectors
2021-09-18 added connectors
2021-09-18 replaced STDC14 with ARM 10pin
2021-09-19 added 10pin debug connector
2021-09-19 added probe holder
2021-09-20 added IO expander parts
2021-09-21 added connectors to part list
2021-09-21 added bus switches to partlist
2021-09-22 changes in partlist
2021-09-22 slight dip switch drawing changes
2021-09-22 added LDO parts
2021-09-22 added component library & testboard schematics
2021-09-22 started design of testboard
2021-09-23 finished testboard schematic
2021-09-23 finished testboard layout
2021-09-23 added projects for probe&target shields
2021-09-23 readme update
2021-09-24 added another connector option
2021-09-24 Testboard layout edits to comply to manufacturer
2021-09-24 added rpi-shield connectors
2021-09-25 finished probe shield schematics
2021-09-25 added daughterboard connector concepts
2021-09-25 added power LED + corrections on probe shield schematics
2021-09-25 started with target stack shield schematics
2021-09-26 naming changes to electrical concept
2021-09-26 further work on target stack shield schematics
2021-09-29 schematic updates, start of probe shield layout
2021-09-29 routing
2021-09-30 changes to connectors
2021-09-30 implemented changes according to feedback, finished target shield schematics
2021-09-30 further work on probe shield layout
2021-09-30 added probe male connector, added 3d models and footprints for shield connectors
2021-10-01 updated testboard schematics to new symbols
2021-10-01 working on pcb layout
2021-10-01 length matching
2021-10-01 probe shield 3d model update
2021-10-04 work on target stack shield layout
2021-10-05 Further work on layout
2021-10-06 finished target stack shield layout
2021-10-06 updates on silkscreen, added 3d renders
2021-10-06 fixed broken silkscreen
2021-10-07 Finished fabrication drawings
2021-10-07 Added 3d assembly and probe holder 3D model
2021-10-07 readme fix
2021-10-07 readme fix 2
2021-10-11 started with daughterboard template
2021-10-11 folder fix
2021-10-12 added preliminary daughterboard template
2021-10-12 started with daughterboard template layout
2021-10-13 finished daughterboard template layout
2021-10-13 git cleanup
2021-10-16 added partlist and prices
2021-10-20 added new daughterboard connector concept
2021-10-27 added cheaper option for 10pin debug connector
2021-10-31 changed PCIE 64 to M.2 Key B connector
2021-10-31 adjusted partlist prices
2021-11-03 added M2.5 Daughterboard backup mounting solution
2021-11-03 updated renders and pictures
2021-11-04 added project library to daughterboard template + minor pcb adjustments
2021-11-05 minor adjustments to daughterboard template, added STM32 daughterboard schematics
2021-11-05 started with LPC daughterboard
2021-11-07 finished LPC Daughterboard schematics
2021-11-07 minor fix to daughterboard template
2021-11-07 started with ATSAMD daughterboard schematics
2021-11-09 further work on ATSAMD daughterboard
2021-11-09 finished ATSAMD daughterboard schematics
2021-11-10 added .gitkeep to empty daughterboard template footprint lib
2021-11-10 started with ESP32/SIFIVE daughterboard
2021-11-11 further work on ESP32/SIFIVE daughterboard
2021-11-12 finished schematics of ESP32_SIFIVE daughterboard
2021-11-12 Minor changes to daughterboard template
2021-11-12 started with NRF daughterboard schematics
2021-11-12 finished NRF daughterboard schematics
2021-11-12 ERC on daughterboards
2021-11-13 added testpoints to daughterboards, updated readme
2021-11-13 finished layout of STM32 daughterboard
2021-11-14 finished ATSAMD daughterboard layout
2021-11-15 sarted with LPC daughterboard layout
2021-11-15 further work on LPC layout
2021-11-16 finsihed LPC daughterboard layout
2021-11-16 started with esp32/sifive layout
2021-11-17 finished ESP32_SIFIVE daughterboard layout
2021-11-17 finished NRF daughterboard layout
2021-11-18 length matching daughterboards
2021-11-18 small corrections to layout
2021-11-19 slight layout adjustments for manufacturing
2021-11-19 minor layout changes to daughterboards for manufacturing
2021-12-03 added definitive led resistor values
2021-12-10 fixed NRF51822 footprint soldermask, fixed SilÃkscreen of ESP32_SIFIVE daughterboard
2021-12-16 updated LED resistor values, updated partlists, minor change to daughterboard template
2021-12-17 added readmes for all Daughterboards
2021-12-17 Daughterboard template readme fix
2021-12-17 Daughterboard template readme fix #2
2021-12-17 Added exact core model to lofive r1 board
2021-12-28 Added STM32 to the Daughterboard table
2022-01-05 added wiki link to readme
2022-01-17 added wiki link to daughterboard readme
2022-01-21 enhanced mechanical PCB drawings of stack shields and daughterboard template
